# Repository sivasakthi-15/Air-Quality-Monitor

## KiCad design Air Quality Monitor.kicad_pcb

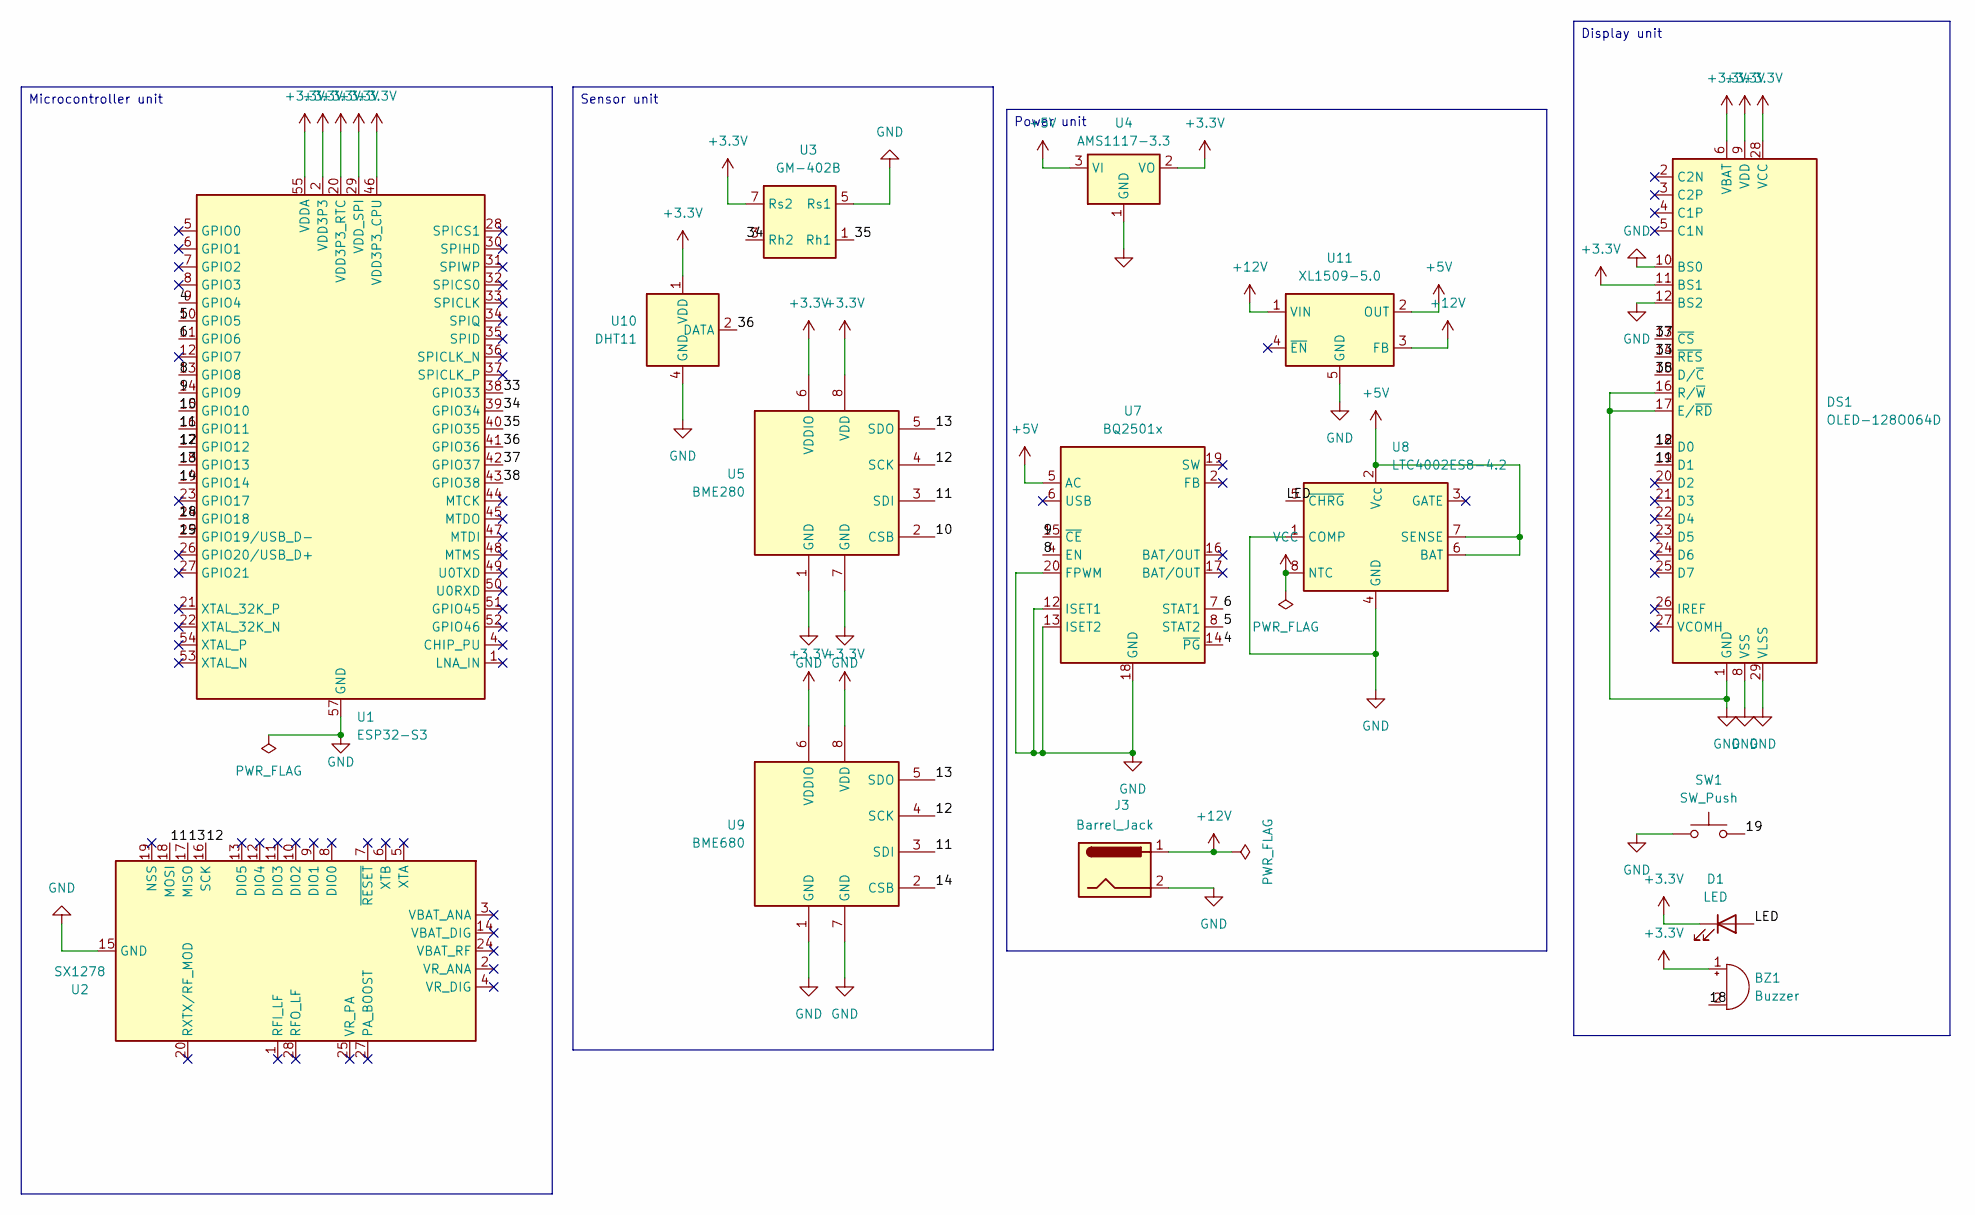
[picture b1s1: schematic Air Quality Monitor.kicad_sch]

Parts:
BZ1: Buzzer; Buzzer_12x9.5RM7.6
D1: LED; LED_0805_2012Metric
DS1: OLED-128O064D
J3: Barrel_Jack; BarrelJack_Horizontal
SW1: SW_Push; SW_PUSH-12mm
U1: ESP32-S3; QFN-56-1EP_7x7mm_P0.4mm_EP4x4mm
U2: SX1278; QFN-28-1EP_6x6mm_P0.65mm_EP4.8x4.8mm
U3: GM-402B; Winson_GM-402B_5x5mm_P1.27mm
U4: AMS1117-3.3; SOT-223-3_TabPin2
U5: BME280; Bosch_LGA-8_2.5x2.5mm_P0.65mm_ClockwisePinNumbering
U7: BQ2501x; Texas_VQFN-RHL-20_ThermalVias
U8: LTC4002ES8-4.2; SOIC-8_3.9x4.9mm_P1.27mm
U9: BME680; Bosch_LGA-8_3x3mm_P0.8mm_ClockwisePinNumbering
U10: DHT11; Aosong_DHT11_5.5x12.0_P2.54mm
U11: XL1509-5.0; SOIC-8_3.9x4.9mm_P1.27mm

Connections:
+3.3V: BZ1.1 (+), D1.1 (K), DS1.6 (VBAT), DS1.9 (VDD), DS1.11 (BS1), DS1.28 (VCC), U1.2 (VDD3P3), U1.3 (VDD3P3), U1.20 (VDD3P3_RTC), U1.29 (VDD_SPI), U1.46 (VDD3P3_CPU), U1.55 (VDDA), U1.56 (VDDA), U3.7 (Rs2), U4.2 (VO), U5.6 (VDDIO), U5.8 (VDD), U9.6 (VDDIO), U9.8 (VDD), U10.1 (VDD)
+5V: U4.3 (VI), U7.5 (AC), U8.2 (V_{CC}), U8.6 (BAT), U8.7 (SENSE), U11.2 (OUT)
+12V: J3.1, U11.1 (VIN), U11.3 (FB)
/4: U1.9 (GPIO4), U7.14 (~PG)
/5: U1.10 (GPIO5), U7.8 (STAT2)
/6: U1.11 (GPIO6), U7.7 (STAT1)
/8: U1.13 (GPIO8), U7.4 (EN)
/9: U1.14 (GPIO9), U7.15 (~CE)
/10: U1.15 (GPIO10), U5.2 (CSB)
/11: DS1.19 (D1), U1.16 (GPIO11), U2.18 (MOSI), U5.3 (SDI), U9.3 (SDI)
/12: DS1.18 (D0), U1.17 (GPIO12), U2.16 (SCK), U5.4 (SCK), U9.4 (SCK)
/13: U1.18 (GPIO13), U2.17 (MISO), U5.5 (SDO), U9.5 (SDO)
/14: U1.19 (GPIO14), U9.2 (CSB)
/18: BZ1.2 (-), U1.24 (GPIO18)
/19: SW1.2, U1.25 (GPIO19/USB_D-)
/33: DS1.14 (~RES), U1.38 (GPIO33)
/34: U1.39 (GPIO34), U3.3 (Rh2)
/35: U1.40 (GPIO35), U3.1 (Rh1)
/36: U1.41 (GPIO36), U10.2 (DATA)
/37: DS1.13 (~CS), U1.42 (GPIO37)
/38: DS1.15 (D/~C), U1.43 (GPIO38)
/LED: D1.2 (A), U8.5 (~CHRG)
GND: DS1.1 (GND), DS1.8 (VSS), DS1.10 (BS0), DS1.12 (BS2), DS1.16 (R/~W), DS1.17 (E/~RD), DS1.29 (VLSS), DS1.30 (GND), J3.2, SW1.1, U1.57 (GND), U2.15 (GND), U2.21 (GND), U2.22 (GND), U2.23 (GND), U2.26 (GND), U2.29 (GND), U3.5 (Rs1), U4.1 (GND), U5.1 (GND), U5.7 (GND), U7.3 (GND), U7.9 (GND), U7.12 (ISET1), U7.13 (ISET2), U7.18 (GND), U7.20 (FPWM), U7.21 (GND), U8.1 (COMP), U8.4 (GND), U9.1 (GND), U9.7 (GND), U10.4 (GND), U11.5 (GND), U11.6 (GND), U11.7 (GND), U11.8 (GND)
VCC: U8.8 (NTC)

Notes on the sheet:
Sensor unit
Microcontroller unit
Power unit
Display unit

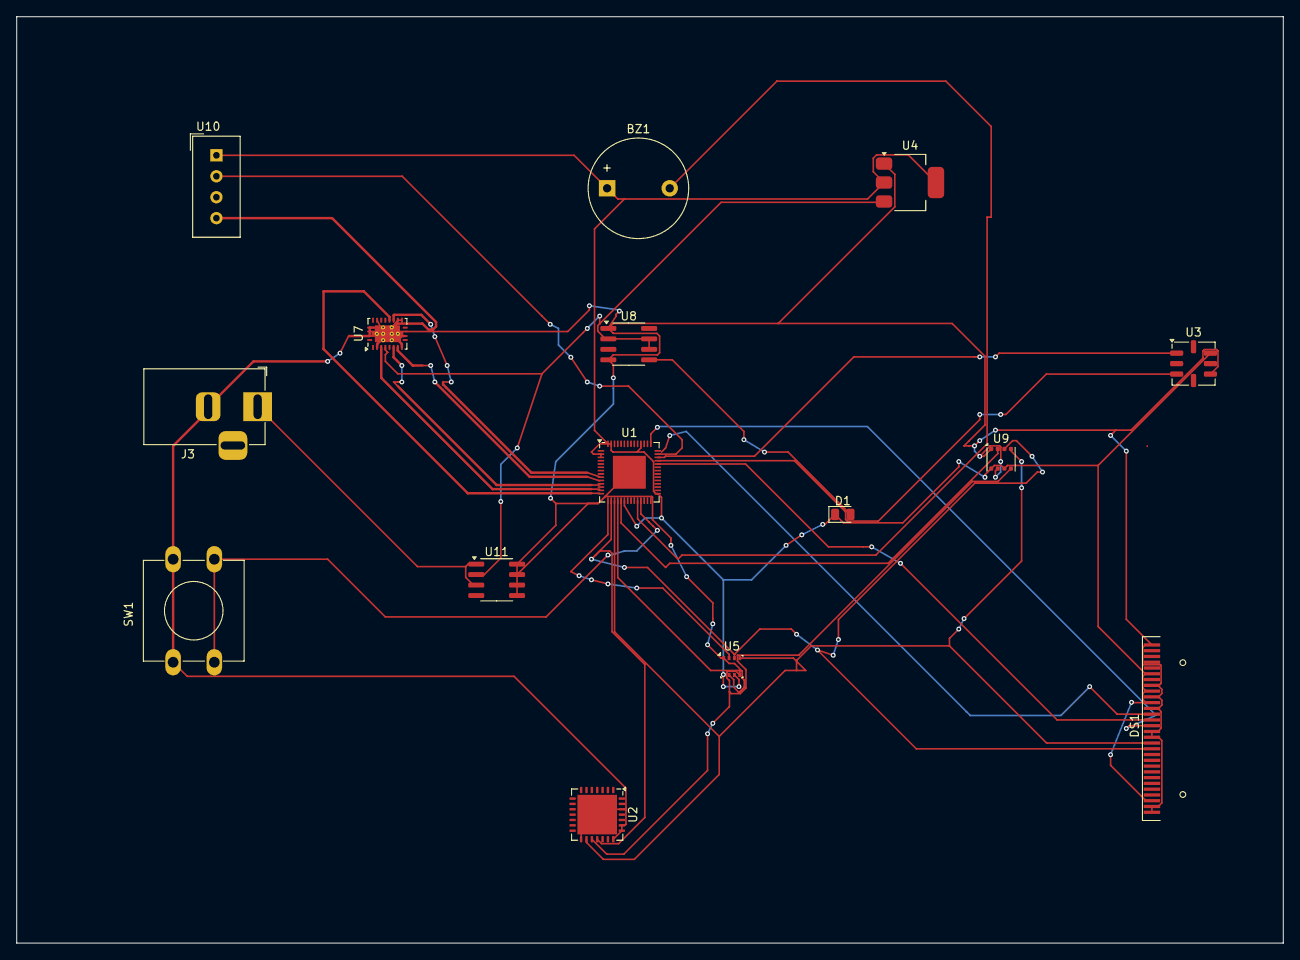
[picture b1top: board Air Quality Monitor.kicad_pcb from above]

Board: 2 copper layers, 153.7 x 112.4 mm, 15 parts (0 on the bottom side), 23 nets.

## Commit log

2025-04-03 Air quality monitor
2025-08-11 Created using Colab
